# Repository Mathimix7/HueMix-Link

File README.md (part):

<h1 align="center">HueMix-Link</h1>

## Table of Contents

- [Quick Start](#quick-start)
- [Project Overview](#project-overview)
- [Screenshots](#screenshots)
- [What Is In This Repository](#what-is-in-this-repository)
- [System Overview](#system-overview)
- [Prerequisites](#prerequisites)
- [Installation](#installation)
- [First-time Commissioning Workflow](#first-time-commissioning-workflow)
- [ESP Firmware: Build and Flash](#esp-firmware-build-and-flash)
- [Firmware Updates (OTA Page)](#firmware-updates-ota-page)
- [Security v2 Protocol](#security-v2-protocol)
- [Configuration and Data Storage](#configuration-and-data-storage)
- [Networking and Ports](#networking-and-ports)
- [How Automation Works](#how-automation-works)
- [Devices](#devices)
- [License](#license)

## Quick Start

1. Install the backend on a Linux host:

 ```bash
  git clone https://github.com/Mathimix7/HueMix-Link.git
  cd HueMix-Link
  sudo bash install.sh
  ```

1. Open the web UI at `http://huemixlink.local` or your server IP.
2. Pair your Hue Bridge from the Bridge configuration page.
3. Put an ESP device into pairing mode and add it from the Pairing page.
4. Configure the device behavior, then verify it by triggering a button, motion sensor, or lightstrip sync.

## Project Overview

HueMix-Link is a local smart home bridge that connects custom ESP-based devices (gateways, buttons, remotes, motion sensors, door sensors, and lightstrips) to Philips Hue rooms and scenes.

It provides:

- A Flask web UI for setup and management
- A UDP server for low-latency gateway communication
- Automation logic for buttons, remotes, and motion sensors
- OTA firmware update workflows for all device types
- Backup and restore tools for configuration data

## Screenshots

<table width="85%" align="center">
  <tr>
    <td colspan="2" align="center">
      
    </td>
  </tr>
  <tr>
    <td width="50%" align="center">
      
    </td>
    <td width="50%" align="center">
      
    </td>
  </tr>
  <tr>
    <td width="50%" align="center">
      
    </td>
    <td width="50%" align="center">
      
    </td>
  </tr>
</table>

## What Is In This Repository

- `python/`: Main backend service (Flask UI + UDP network + automations + OTA)
- `esp-firmware/`: PlatformIO firmware sources for all device types (gateway, buttons, remotes, motion sensors, door sensors, lightstrips)
- `Hardware-designs/`: KiCad design files for all device types (gateway, buttons, remotes, motion sensors, door sensors, lightstrips)
- `3D Files/`: 3D model files for all device types (STL format for 3D printing)
- `install.sh`: Linux installer/updater
- `VERSION`: Version file for installer/update workflows

## System Overview

### High-level architecture

1. **All ESP devices use ESP-NOW**: Low-power mesh protocol for device-to-device communication
2. **Gateways bridge ESP-NOW to UDP**: Gateways receive ESP-NOW messages and forward them to the backend via UDP
3. **Backend (UDP server) receives events**: Button presses, remote actions, motion detections, device hellos, delivery reports
4. **Automation engine maps events to Hue actions**: Scene activation, toggle on/off, brightness adjust, and lightstrip sync
5. **Hue state is cached and synchronized**: Automations and lightstrips stay aligned with current room/scene state
6. **Web UI for management**: Device pairing, automation configuration, OTA updates, monitoring, and backups

### Main runtime services

- **Flask + Waitress**: Web UI server `127.0.0.1:5001` (default)
- **UDP listener**: Receives gateway messages on `0.0.0.0:7777` (default, configurable)
- **Automation service**: Listens to device events and Hue state changes, applies configured logic
- **OTA manager**: Handles firmware distribution, chunking, and acknowledgment tracking

## Prerequisites

### Software

- Python 3.9+ (3.10+ recommended)
- `pip` and virtual environment support (`venv`)
- Network access to your Hue Bridge (same LAN)
- Linux OS with `systemd` (for production install)
- `sudo` access and `apt` package manager

### Hardware

- At least one Hue Bridge with configured rooms/scenes
- Supported HueMix-Link devices (gateways, buttons, remotes, motion sensors, door sensors, lightstrips)
- Firmware binaries matching your device type and model

## Installation

### Linux

From the repository root:

```bash
sudo bash install.sh
```

The installer will:

- Deploy the Python app to `/opt/huemix-link`
- Create a dedicated service user and Python virtual environment
- Set up a `systemd` service (`huemix-link`) to run on boot
- Configure HAProxy to expose the web app (HTTP port 80, HTTPS port 443 by default)
- Store all runtime data in `/opt/huemix-link/data`

Useful installer options:

```bash
sudo bash install.sh --help           # Show all options
sudo bash install.sh --yes            # Non-interactive install
sudo bash install.sh --dry-run        # Preview without making changes
sudo bash install.sh --force          # Force recreation of venv
sudo bash install.sh --show-version   # Show installed and source versions
sudo bash install.sh --port 8080      # Expose on custom HTTP port
sudo bash install.sh --no-https       # Disable HTTPS (HTTP only)
sudo bash install.sh --no-local       # Skip huemixlink.local hostname setup
```

After installation, the web UI is accessible at:

- `https://huemixlink.local` (or your server IP)
- `http://huemixlink.local` (or your server IP)

### Updating

To update the backend to a newer version, pull the latest code and re-run the installer:

```bash
git pull
sudo bash install.sh
```

The installer detects the existing installation, updates the files, and restarts the service automatically.

## First-time Commissioning Workflow

1. **Start the backend** (automatic on boot if installed via installer)
2. **Open the web UI** at `http://huemixlink.local` (or your server IP)
3. **Configure Hue Bridge**:
   - Go to the Bridge configuration page
   - Auto-discover or enter bridge IP manually
   - Press the Hue Bridge link button
   - Pair app with bridge (saves credentials)
4. **Pair ESP devices**:
   - Go to Pairing page
   - Start pairing window (choose device type if desired)
   - Power on or reset target devices
   - Devices announce themselves via ESP-NOW → gateway → backend
5. **Configure each device**:
    - **Buttons/Remotes**: Map to room + scenes + action behavior (normal, toggle, brightness, scene-cycle)
    - **Motion Sensors**: Set room, time slots, motion actions, after-actions, cooldown periods
    - **Door Sensors**: Set room, open/close actions, and any automation triggers tied to magnetic state changes
    - **Lightstrips**: Assign room, configure LED count/type, optional color scene overrides
    - **Gateways**: Verify online status, mesh routing, LED schedule (day/night auto-off)
6. **Validate behavior** by triggering physical events and checking Hue room/scene changes

## ESP Firmware: Build and Flash

### Flashing ESP devices

**Option 1: Serial flash via OTA page**

1. Go to the **OTA** page in the web UI
2. Select firmware type
3. Connect ESP device via serial in programming mode
4. Click **Flash** and select serial port
5. Monitor progress on the page

**Option 2: Serial port flash**

Use PlatformIO to flash directly via USB:

```bash
cd esp-firmware
pio run -e esp32_net_node --target upload
```

Or use `esptool.py` directly:

```bash
esptool.py --port /dev/ttyUSB0 write_flash 0x0 huemixlink-esp32-net-vX.Y.Z.bin
```

Pre-built firmware binaries are available in the project's GitHub releases. Download the `.bin` file(s) matching your device type and platform.

## Firmware Updates (OTA Page)

The **OTA** page in the web UI lets you:

- **Check available versions** from GitHub releases
- **Web Serial Flasher**: Flash ESP32/ESP8266 devices directly from the browser; v4.x non-gateway firmwares automatically provision a unique 6-digit Security v2 PIN, with one-click **Copy PIN**, **Copy NFC Pairing URL**, and **Print Label** (QR code + PIN)
- **Queued & wake-triggered OTA**: Queue multiple device updates (runs one at a time, automatically ordering radio node before net node on gateways); battery-powered v2 devices can wake and pull queued updates automatically (with a 20% minimum battery guard)
- **Fast v2 OTA**: ESP32 devices on Security v2 use ESP-NOW v2 frames (up to 1024-byte chunks) for 3–5× faster wireless updates
- **Security upgrades & PIN management**: Trigger in-place v1 → v2 upgrades, provision/view 6-digit PINs, and print pairing labels directly from the device list

## Security v2 Protocol

Firmware `4.x` introduces **Security v2**, an authenticated encryption layer over ESP-NOW and UDP that replaces legacy v1 FNV-1a checksums while remaining dual-stack compatible during migration:

- **Authenticated encryption & replay protection**: Every v2 device derives unique per-device `K_own` and `K_ack` keys (via HKDF from the server's master key) during an **X25519 ECDH** 3-flight handshake. All packets are encrypted and authenticated with **AES-128-GCM** and protected against replay attacks by monotonic counters persisted on flash and SQLite.
- **6-digit device PINs**: Non-gateway devices support a write-once 6-digit pairing PIN (auto-provisioned during Web Serial Flashing or sent over an encrypted v2 link from the OTA page) that binds the ECDH handshake against MITM attacks.
- **QR labels & NFC tap-to-pair**: Printable labels include a QR code pointing to `/pairing#pin=XXXXXX`, and the same URL can be written to NTAG NFC stickers. Scanning a label or tapping an NFC tag opens `/pairing` and automatically starts a 60-second v2 pairing window with that PIN (using the `#` URL fragment keeps the PIN out of HTTP server logs).
- **TOFU-only gateways**: Local LAN WiFi and Serial gateways use TOFU Security v2 and auto-pair without requiring PINs.
- **Secure Short-Range Auto-Pairing**: An optional toggle on `/pairing` allows non-revoked Security v2 devices with a saved 6-digit PIN and signal stronger than `-50 dBm` to auto-pair without opening a long-range window (legacy v1, TOFU, and revoked devices are blocked).
- **Migration controls**: Settings provides toggles to enable v2 pairing, require v2 for new pairings, or disable legacy v1 traffic once all devices are upgraded.

## Configuration and Data Storage

All runtime configuration is stored in `python/data/` (or `/opt/huemix-link/data` in production) as JSON files:

- `bridge.json`: Hue bridge IP and app username
- `config.json`: Server settings (UDP port, dev mode)
- `gateways.json`: Known gateway devices
- `buttons.json`: Button and remote configurations
- `motion_sensors.json`: Motion sensor configurations and time slots
- `lightstrips.json`: Lightstrip configurations and color overrides
- `pairing_history.json`: Last 5 paired devices
- `home_id`: Unique 32-bit network identifier for this HueMix-Link instance. In legacy protocol v1, it is mixed into the FNV-1a packet checksum to separate installations (**HomeID is a network identifier, not a cryptographic secret**). See [Security v2 Protocol](#security-v2-protocol) for authenticated encryption.

Backups are created and restored through the settings page; they are stored in `data/backups/`.

## Networking and Ports

- **Web server (internal)**: `127.0.0.1:5001` (Flask)
- **UDP listener (internal)**: `0.0.0.0:7777` (default, receives gateway messages)
- **External HTTP/HTTPS (production)**: Exposed by HAProxy (default HTTP 80 + HTTPS 443)

UDP port can be changed in settings; the backend will restart UDP listening with the new port.

## How Automation Works

1. **Device sends event** via **ESP-NOW** (button press, remote action, motion detection)
2. **Gateway receives** via ESP-NOW and forwards message to backend via **UDP**
3. **UDP server** decodes and validates packet (AES-128-GCM authentication in Security v2, or HomeID checksum in legacy v1)
4. **Device manager** resolves device identity; **pairing manager** verifies eligibility
5. **Automation engine** applies configured logic:
   - **Buttons/Remotes**: Scene cycle, toggle, brightness adjust, hold-to-adjust
   - **Motion Sensors**: Trigger scenes/lights on detection; post-motion fade/off actions; cooldown throttling
6. **Hue API** is called to apply scene/room/light changes
7. **Hue state manager** caches current room, light, and scene state
8. **Lightstrip sync**: Checks if any lightstrips should mirror current scene; sends raw LED commands via **ESP-NOW → gateway → UDP**

On startup, config sync reconciles saved room/scene references against live Hue topology to avoid stale mappings.

## Devices

### Gateway

<table><tr>
  <td></td>
  <td></td>
</tr></table>

The Gateway is a single board that contains two ESP32 modules working together:

- **Net Node** — connects to your home WiFi and bridges between the backend (UDP) and the ESP-NOW mesh. Runs WiFiManager for wireless configuration and relays commands to the radio node over a high-speed UART link.
- **Radio Node** — handles all ESP-NOW communication with peripheral devices (buttons, remotes, sensors, lightstrips) and forwards packets to/from the net node over UART. Extends ESP-NOW coverage independently of WiFi.

**LED indicators**

| LED | State | Meaning |
| ----- | ------- | --------- |
| WiFi | Off | No power / booting |
| WiFi | Fast blink (0.2s) | Not yet configured — WiFi config portal is open |
| WiFi | Slow blink (0.5s) | Connecting or retrying WiFi |
| WiFi | Solid on | Online and operational |
| Data | Brief flash | Packet received or forwarded |
| Data | Breathing (fade in/out) | Net node OTA firmware update in progress |
| Radio | Brief flash | ESP-NOW packet relayed |
| Radio | Breathing (fade in/out) | Radio node OTA firmware update in progress |

**Buttons**

- **Main button**: Acts as a single button that can be mapped to a Hue room in the web UI
- **Aux button**: Hold 5+ seconds to factory-reset and re-open the WiFi config portal

**Initial setup**

1. Power on the gateway — the WiFi LED fast-blinks and it broadcasts SSID `HueMix Link - XXXXXXXX`
2. Connect to that SSID (password: `HueMixLink`) with a phone or laptop
3. Enter your home WiFi credentials and the backend server IP + UDP port
4. The gateway connects, the WiFi LED goes solid, and it sends a HELLO to the backend

**Pairing**

Gateways pair automatically once configured.

**OTA**

Both nodes are updated from the OTA page. Gateways receive OTA directly (no double-press needed).

---

### Radio Gateway (Serial Python)

The Radio Gateway can also run as a serial-connected ESP32 node that pairs with the Python backend instead of WiFi.

- **Net/host side**: Python maintains the gateway state, serial transport, OTA scheduling, and dashboard telemetry
- **Radio side**: ESP32 radio node handles ESP-NOW traffic, OLED status display, and forwards packets over UART
- **LED indicators**: Follows the configured gateway LED schedule; the OLED display also respects the same on/off timing
- **OTA**: Updated from the OTA page using the `gateway_radio_python` firmware target

**Setup**

1. Flash the `esp32_radio_python` firmware
2. Connect the radio node to the backend host over USB serial
3. Configure the serial port in the web UI
4. The backend will sync HOME_ID, gateway state, and dashboard telemetry automatically

---

### Button

<table><tr>
  <td></td>
  <td></td>
</tr></table>

The Button is a single pushbutton device that sends click, hold, and release events via ESP-NOW. The ESP32 version is battery-powered and deep-sleeps between presses, while the ESP8266 version is always-on and runs continuously.

> [!WARNING]
> The `normal_button` firmware is deprecated. The ESP32 Normal Button board v3 and later should use the `remote_button` firmware configured as 1, 2, or 3 buttons.

**Events sent**

| Action | Trigger |
| -------- | --------- |
| Click | Short press and release |
| Holding | Held beyond 500 ms, repeated every 500 ms |
| Release | Released after a hold |

**Default automation** (configurable in web UI): Click cycles scenes in the assigned room. Hold adjusts brightness. Release stops brightness adjustment.

**LED indicators**

| State | Meaning |
| ------- | --------- |
| Brief flash | Action sent via ESP-NOW |
| 2 fast blinks | No acknowledgment — gateway may be out of range |
| 2 slow blinks | Failed to pair device |
| 3 blinks | OTA mode |
| 5 blinks | Device powered on |
| Breathing | OTA in progress |

**Setup and pairing**

1. Flash firmware via serial or the OTA page
2. Open the Pairing page, start a pairing window, then press the button to wake the device
3. After pairing, assign the button to a room in the device settings

**OTA**

**Double-press the reset button** to enter OTA mode — the LED will blink 3 times to confirm. Then initiate the flash from the OTA page.

---

### Remote

<table><tr>
  <td></td>
  <td></td>
</tr></table>

The Remote is a battery-powered ESP32 device with up to 4 independently configurable buttons. Each button can target a different room with its own action type. The number of active buttons (1–4) is configured via hardware at flash time.

**Action types per button** (configurable in web UI)

| Type | Click | Hold |
| ------ | ------- | ------ |
| Normal | Cycle scenes / turn room off | Adjust brightness |
| Toggle | Toggle room on/off | — |
| Brightness Up | Increase brightness | Increase continuously |
| Brightness Down | Decrease brightness | Decrease continuously |
| Scene Cycle | Cycle scenes (no off) | Adjust brightness |

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
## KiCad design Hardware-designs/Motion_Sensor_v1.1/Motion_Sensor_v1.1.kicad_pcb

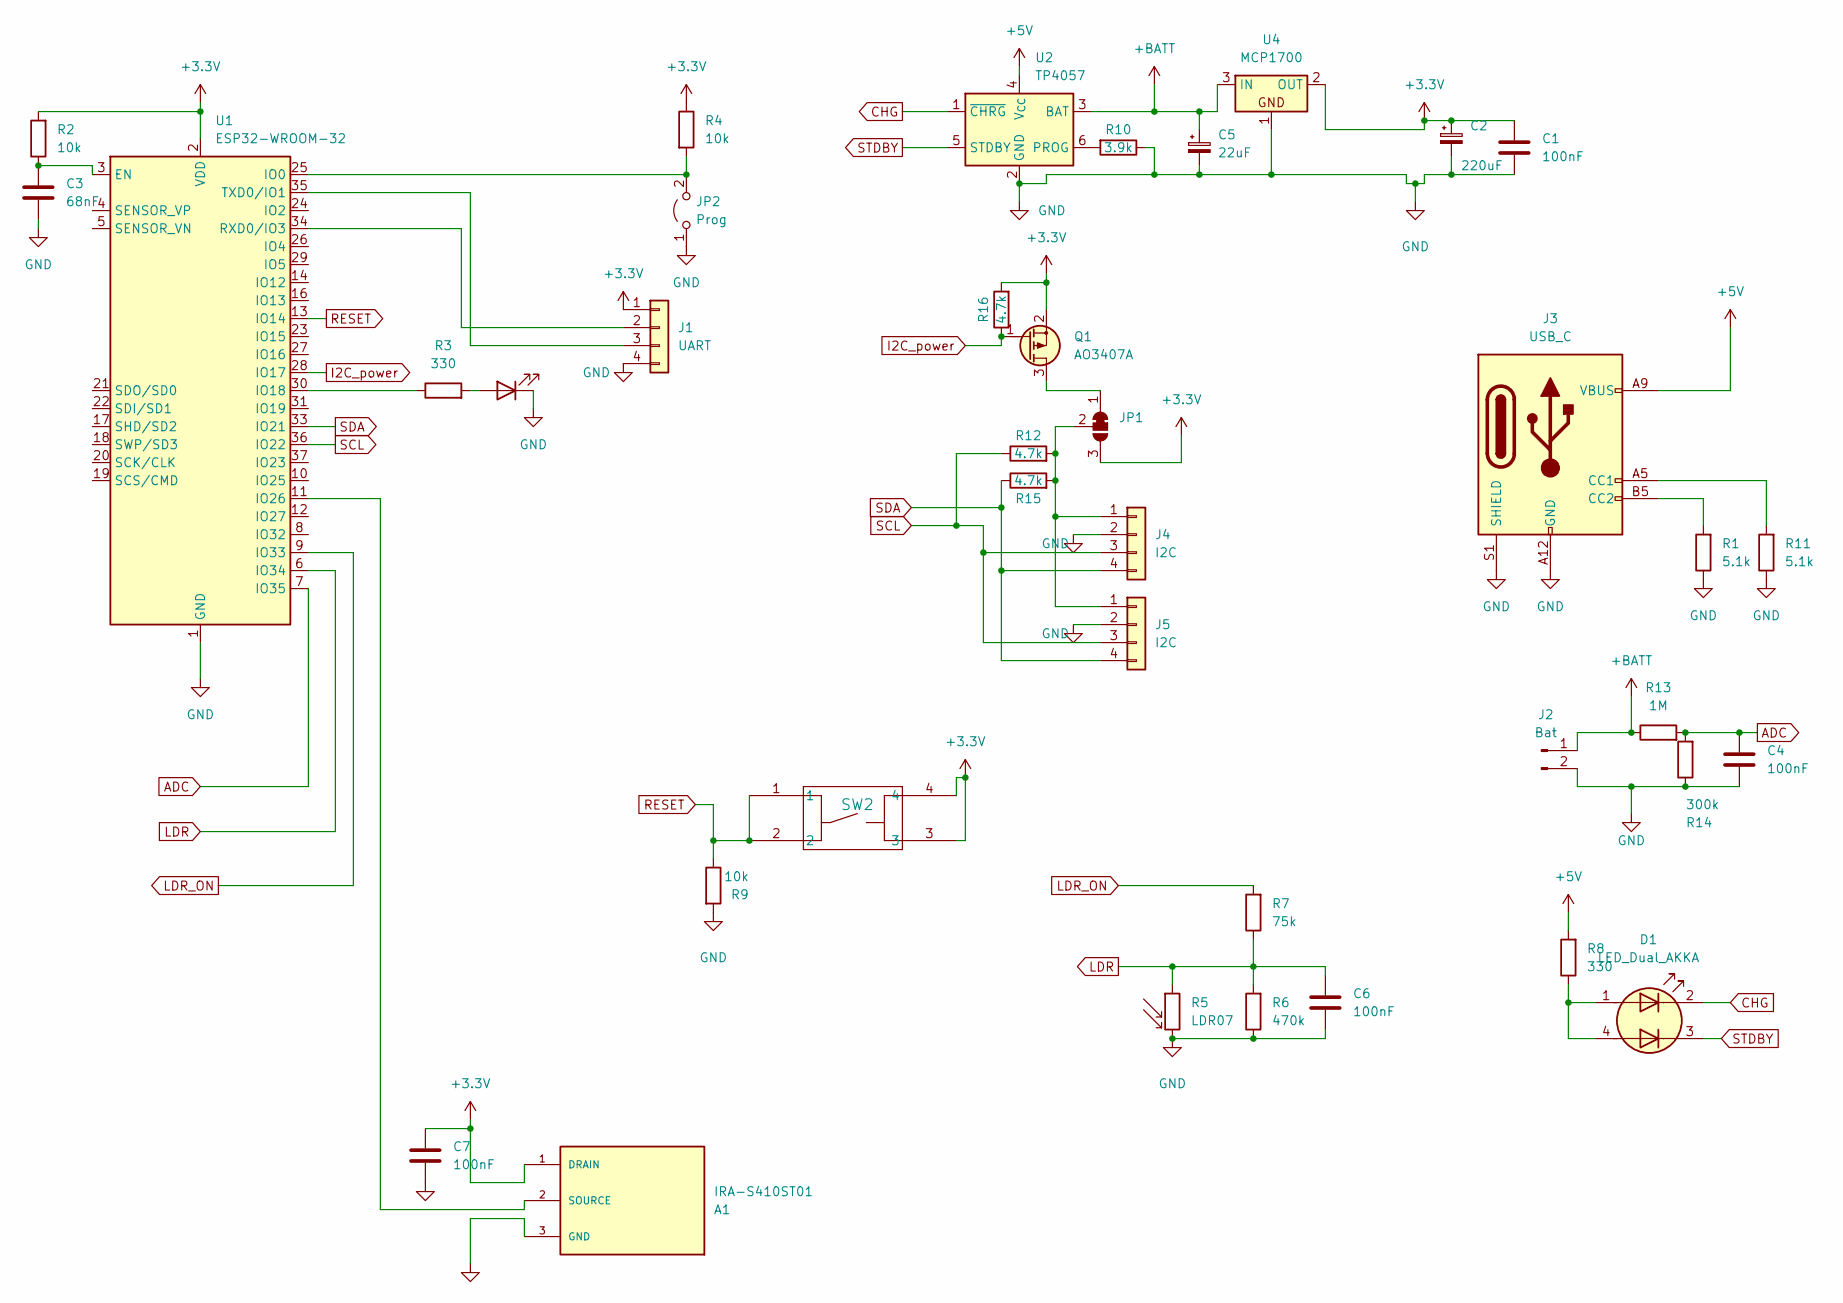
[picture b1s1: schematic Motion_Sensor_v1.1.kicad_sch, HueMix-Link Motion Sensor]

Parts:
A1: IRA-S410ST01; TO254P940H490-3
C1, C4, C6, C7: 100nF; C_0805_2012Metric_Pad1.18x1.45mm_HandSolder
C2: 220uF; CP_EIA-6032-15_Kemet-U_HandSolder
C3: 68nF; C_0805_2012Metric_Pad1.18x1.45mm_HandSolder
C5: 22uF; CP_EIA-6032-15_Kemet-U_HandSolder
D1: LED_Dual_AKKA; APHBM2012ETSGTC
D3: LED; LED_1206_3216Metric
J1: UART; PinHeader_1x04_P2.54mm_Vertical
J2: Bat; TestPoint_2Pads_Pitch2.54mm_Drill0.8mm
J3: USB_C; USB_C_Receptacle_GCT_USB4125-xx-x-0190_6P_TopMnt_Horizontal
J4, J5: I2C; PinHeader_1x04_P2.54mm_Vertical
JP1: SolderJumper_3_Bridged12; SolderJumper-3_P1.3mm_Bridged12_RoundedPad1.0x1.5mm
JP2: Prog; PinHeader_1x02_P2.54mm_Vertical
Q1: AO3407A; SOT-23
R1, R11: 5.1k; R_1206_3216Metric_Pad1.30x1.75mm_HandSolder
R2, R4, R9: 10k; R_1206_3216Metric_Pad1.30x1.75mm_HandSolder
R3, R8: 330; R_1206_3216Metric_Pad1.30x1.75mm_HandSolder
R5: LDR07; R_LDR_5.1x4.3mm_P3.4mm_Vertical
R6: 470k; R_1206_3216Metric_Pad1.30x1.75mm_HandSolder
R7: 75k; R_1206_3216Metric_Pad1.30x1.75mm_HandSolder
R10: 3.9k; R_1206_3216Metric_Pad1.30x1.75mm_HandSolder
R12, R15, R16: 4.7k; R_1206_3216Metric_Pad1.30x1.75mm_HandSolder
R13: 1M; R_1206_3216Metric_Pad1.30x1.75mm_HandSolder
R14: 300k; R_1206_3216Metric_Pad1.30x1.75mm_HandSolder
SW2: PTS526 SM15 SMTR2 LFS; SMT_FS
U1: ESP32-WROOM-32; ESP32-WROOM-32D
U2: TP4057; TSOT-23-6_HandSoldering
U4: MCP1700; SOT-23

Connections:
+3.3V: A1.1 (DRAIN), C1.1, C2.1, C7.1, J1.1, JP1.3 (B), Q1.2 (S), R2.2, R4.1, R16.2, SW2.3, SW2.4, U1.2 (VDD), U4.2 (OUT)
+5V: J3.A9 (VBUS), J3.B9 (VBUS), R8.2, U2.4 (V_{CC})
+BATT: C5.1, J2.1, R13.1, U2.3 (BAT), U4.3 (IN)
ADC: C4.1, R13.2, R14.2, U1.7 (IO35)
CHG: D1.2 (K1), U2.1 (~CHRG)
GND: A1.3 (GND), C1.2, C2.2, C3.2, C4.2, C5.2, C6.2, C7.2, D3.1 (K), J1.4, J2.2, J3.A12 (GND), J3.B12 (GND), J3.S1 (SHIELD), J4.2, J5.2, JP2.1 (A), R1.1, R5.2, R6.1, R9.2, R10.1, R11.1, R14.1, U1.1 (GND), U1.15 (GND), U1.38 (GND), U1.39 (GND), U2.2 (GND), U4.1
I2C_power: Q1.1 (G), R16.1, U1.28 (IO17)
LDR: C6.1, R5.1, R6.2, R7.1, U1.6 (IO34)
LDR_ON: R7.2, U1.9 (IO33)
unnamed: A1.2 (SOURCE), U1.11 (IO26)
unnamed: D1.1 (A1), D1.4 (A2), R8.1
unnamed: D3.2 (A), R3.2
unnamed: J1.2, U1.34 (RXD0/IO3)
unnamed: J1.3, U1.35 (TXD0/IO1)
unnamed: J3.A5 (CC1), R11.2
unnamed: J3.B5 (CC2), R1.2
unnamed: J4.1, J5.1, JP1.2 (C), R12.2, R15.2
unnamed: JP1.1 (A), Q1.3 (D)
unnamed: JP2.2 (B), R4.2, U1.25 (IO0)
unnamed: C3.1, R2.1, U1.3 (EN)
unnamed: R3.1, U1.30 (IO18)
unnamed: R10.2, U2.6 (PROG)
RESET: R9.1, SW2.1, SW2.2, U1.13 (IO14)
SCL: J4.3, J5.3, R12.1, U1.36 (IO22)
SDA: J4.4, J5.4, R15.1, U1.33 (IO21)
STDBY: D1.3 (K2), U2.5 (STDBY)

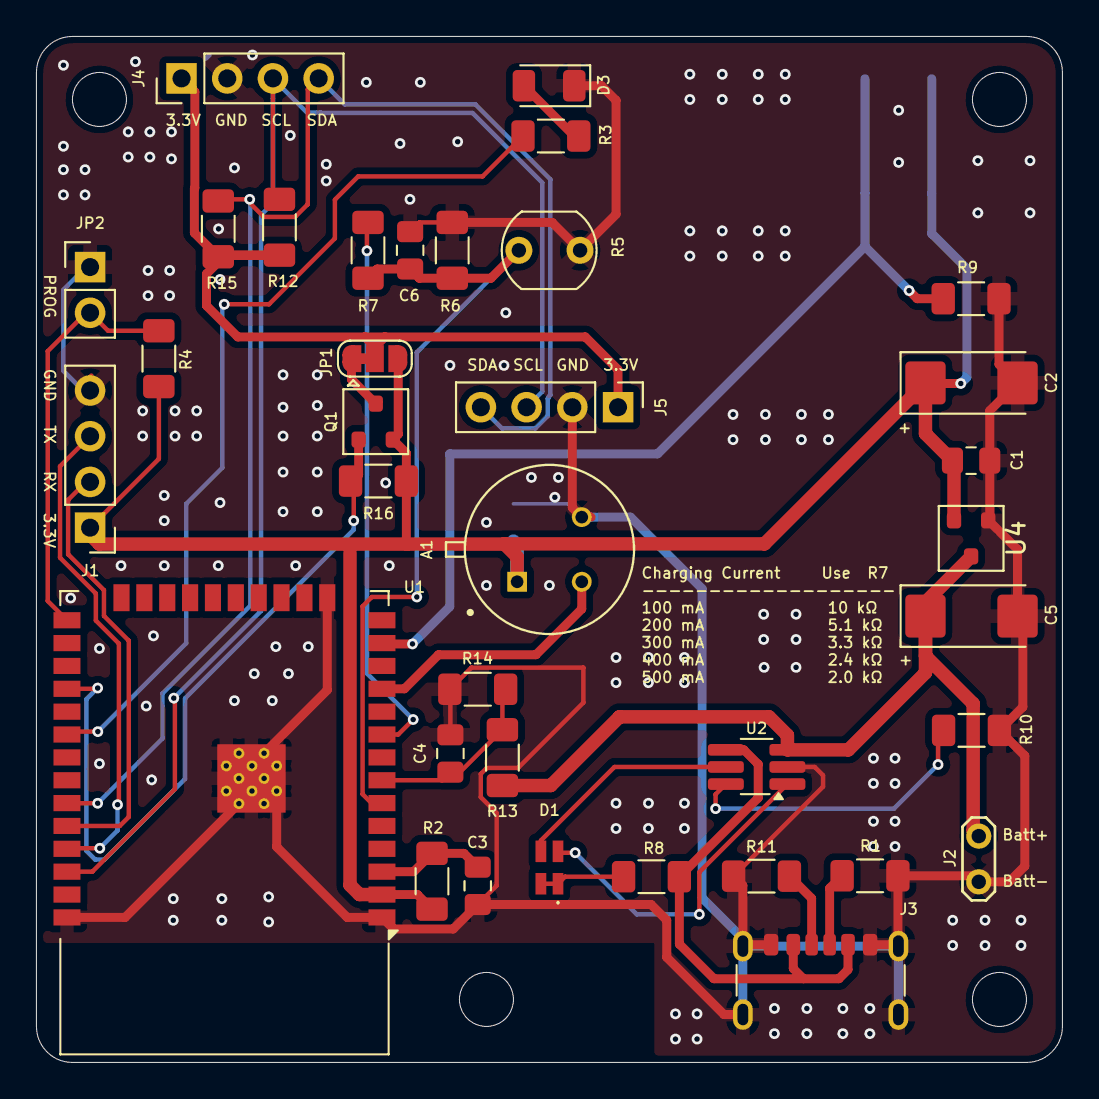
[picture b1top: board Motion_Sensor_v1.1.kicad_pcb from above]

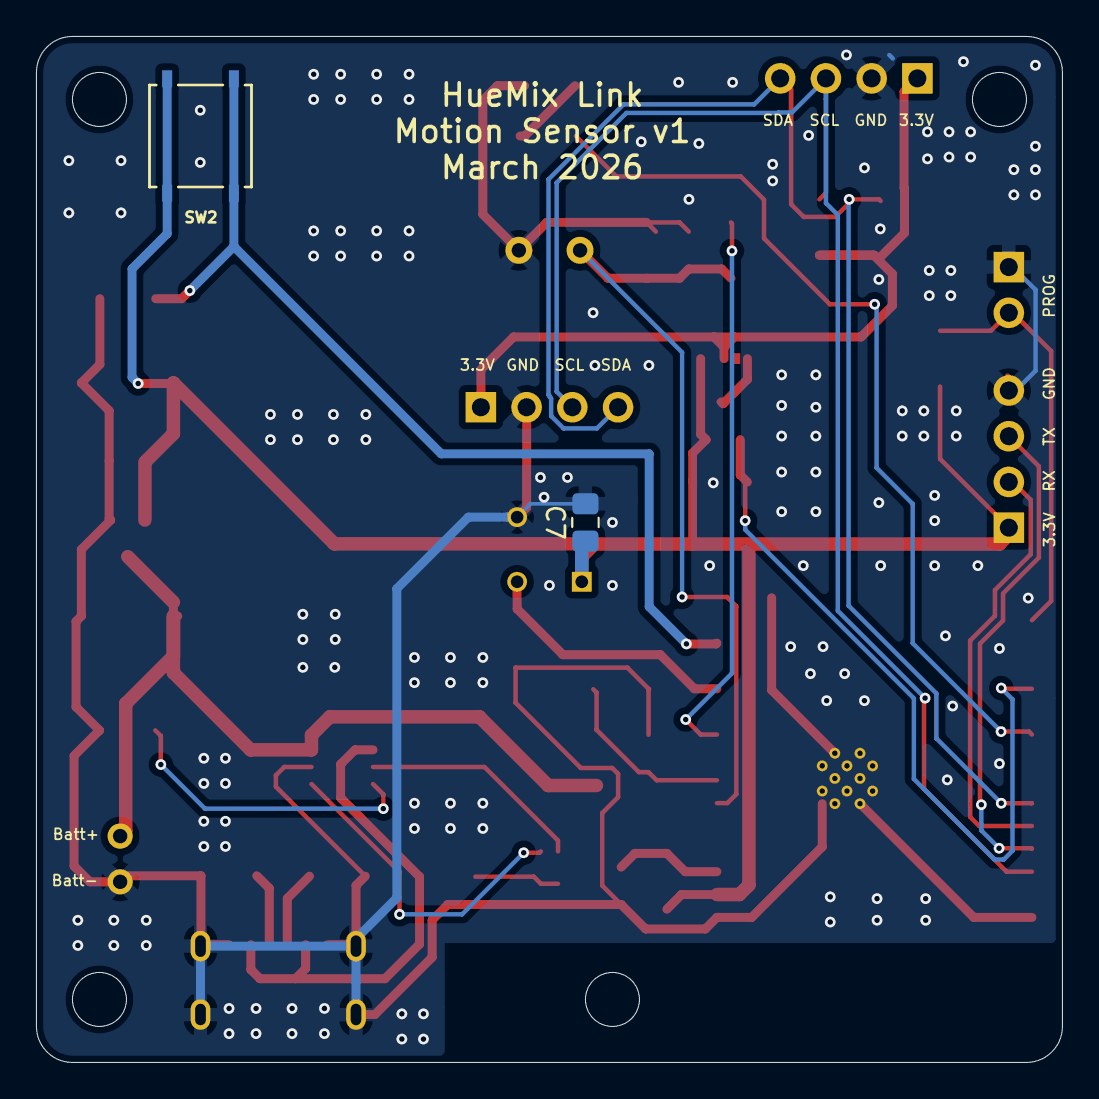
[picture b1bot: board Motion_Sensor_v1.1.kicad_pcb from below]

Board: 2 copper layers, 57.0 x 57.0 mm, 38 parts (2 on the bottom side), 26 nets.

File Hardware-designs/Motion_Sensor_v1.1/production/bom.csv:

Designator,Footprint,Quantity,Value,LCSC Part #
A1,TO254P940H490-3,1,IRA-S410ST01,
"C1, C4, C6, C7",0805,4,100nF,
C2,CP_EIA-6032-15_Kemet-U_HandSolder,1,220uF,
C3,0805,1,68nF,
C5,CP_EIA-6032-15_Kemet-U_HandSolder,1,22uF,
D1,APHBM2012ETSGTC,1,LED_Dual_AKKA,
D3,1206,1,LED,
J1,PinHeader_1x04_P2.54mm_Vertical,1,UART,
J2,TestPoint_2Pads_Pitch2.54mm_Drill0.8mm,1,Bat,
J3,USB_C_Receptacle_GCT_USB4125-xx-x-0190_6P_TopMnt_Horizontal,1,USB_C,
"J4, J5",PinHeader_1x04_P2.54mm_Vertical,2,I2C,
JP2,PinHeader_1x02_P2.54mm_Vertical,1,Prog,
Q1,SOT-23,1,AO3407A,
"R1, R11",1206,2,5.1k,
R10,1206,1,3.9k,
"R12, R15, R16",1206,3,4.7k,
R13,1206,1,1M,
R14,1206,1,300k,
"R2, R4, R9",1206,3,10k,
"R3, R8",1206,2,330,
R5,R_LDR_5.1x4.3mm_P3.4mm_Vertical,1,LDR07,
R6,1206,1,470k,
R7,1206,1,75k,
SW2,SMT_FS,1,PTS526 SM15 SMTR2 LFS,
U1,ESP32-WROOM-32D,1,ESP32-WROOM-32,
U2,TSOT-23-6_HandSoldering,1,TP4057,
U4,SOT-23,1,MCP1700,

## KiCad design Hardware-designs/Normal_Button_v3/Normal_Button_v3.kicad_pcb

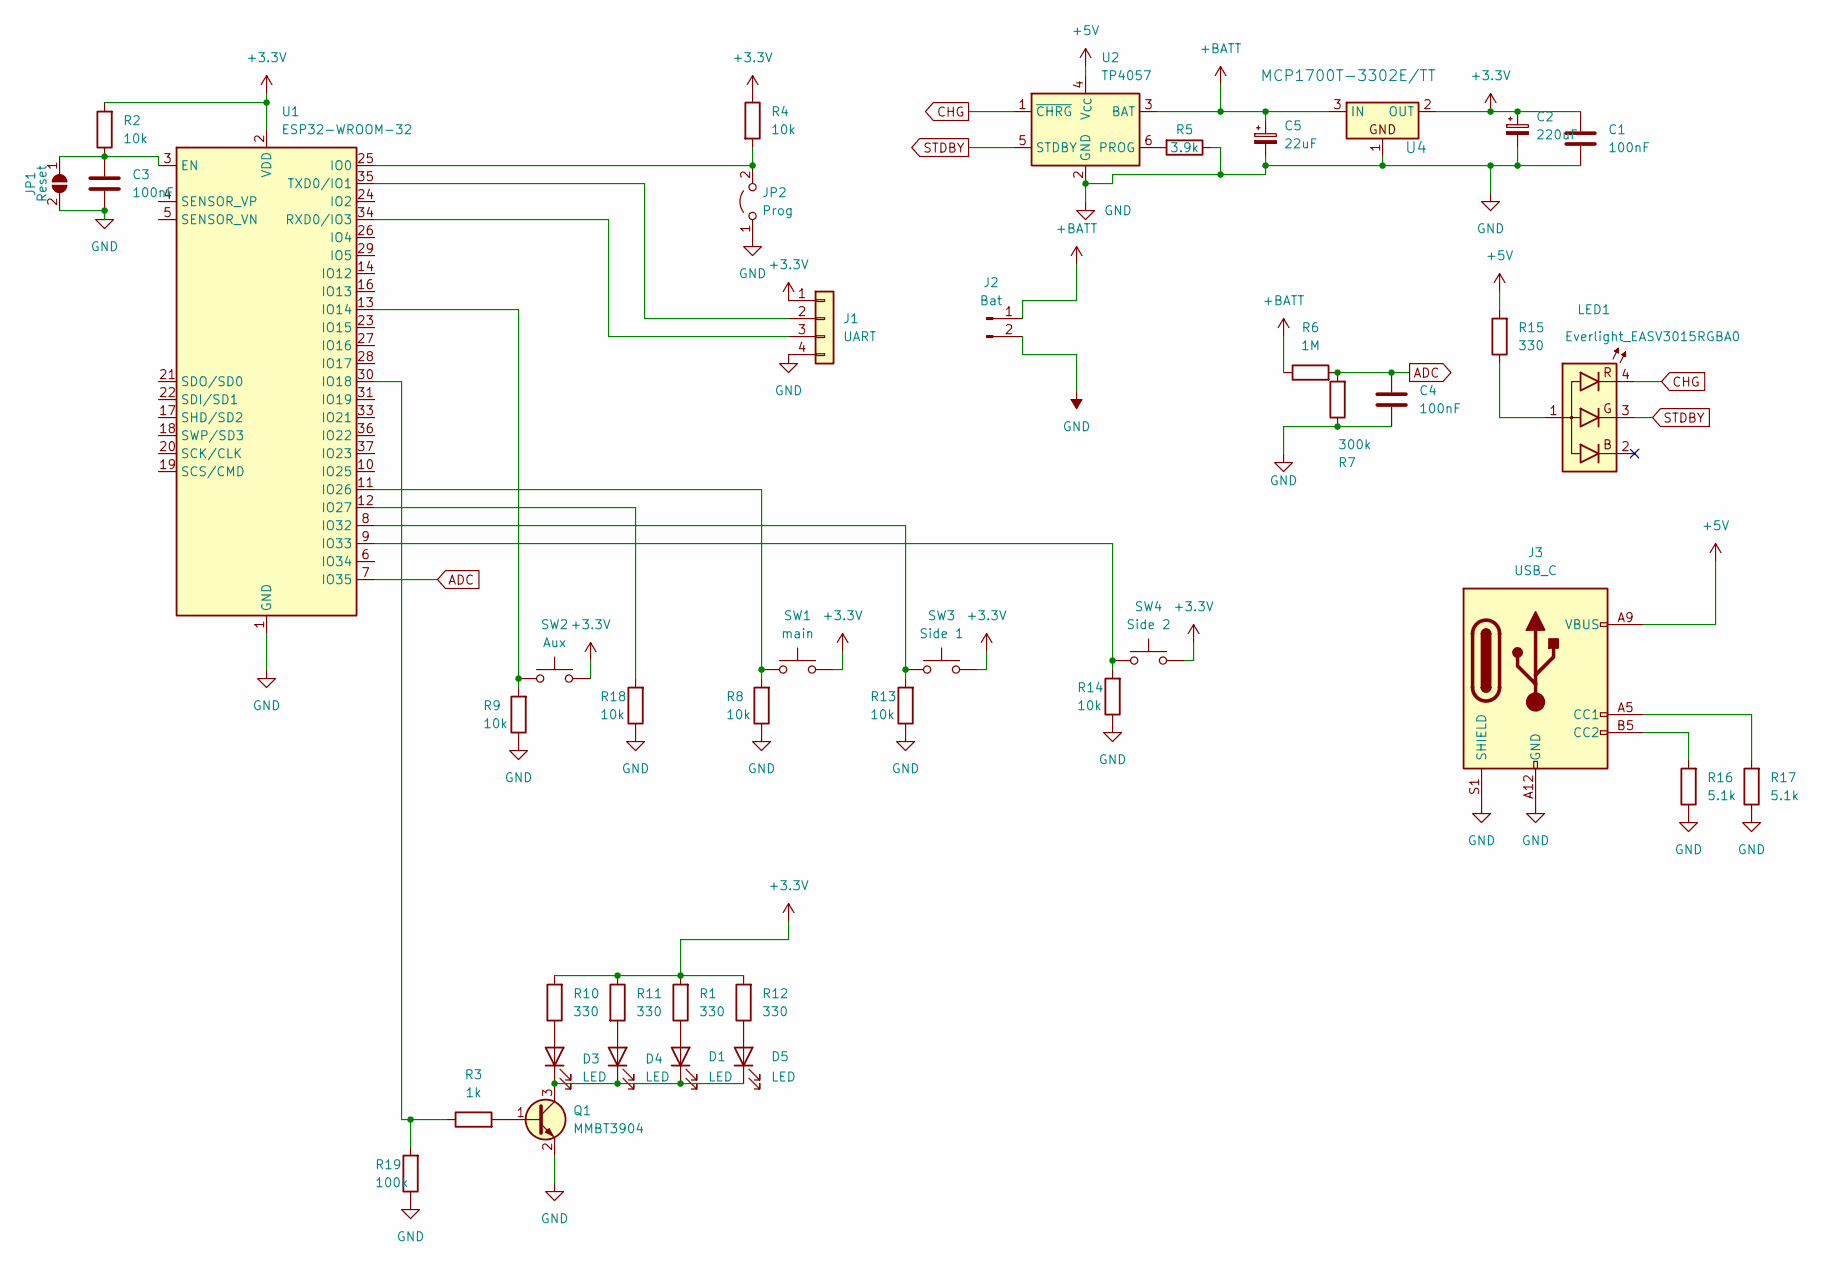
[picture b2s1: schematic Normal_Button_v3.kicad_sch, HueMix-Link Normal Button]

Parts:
C1, C3, C4: 100nF; C_0805_2012Metric_Pad1.18x1.45mm_HandSolder
C2: 220uF; CP_EIA-6032-15_Kemet-U_HandSolder
C5: 22uF; CP_EIA-6032-15_Kemet-U_HandSolder
D1, D3, D4, D5: LED; LED_D3.0mm
J1: UART; PinHeader_1x04_P2.54mm_Vertical
J2: Bat; JST_EH_B2B-EH-A_1x02_P2.50mm_Vertical
J3: USB_C; USB_C_Receptacle_GCT_USB4125-xx-x-0190_6P_TopMnt_Horizontal
JP1: Reset; SolderJumper-2_P1.3mm_Open_Pad1.0x1.5mm
JP2: Prog; PinHeader_1x02_P2.54mm_Vertical
LED1: Everlight_EASV3015RGBA0; LED_D5.0mm-4_RGB
Q1: MMBT3904; SOT-23
R1, R10, R11, R12, R15: 330; R_1206_3216Metric_Pad1.30x1.75mm_HandSolder
R2, R4, R8, R9, R13, R14, R18: 10k; R_1206_3216Metric_Pad1.30x1.75mm_HandSolder
R3: 1k; R_1206_3216Metric_Pad1.30x1.75mm_HandSolder
R5: 3.9k; R_1206_3216Metric_Pad1.30x1.75mm_HandSolder
R6: 1M; R_1206_3216Metric_Pad1.30x1.75mm_HandSolder
R7: 300k; R_1206_3216Metric_Pad1.30x1.75mm_HandSolder
R16, R17: 5.1k; R_1206_3216Metric_Pad1.30x1.75mm_HandSolder
R19: 100k; R_1206_3216Metric_Pad1.30x1.75mm_HandSolder
SW1: main; SW_PUSH-12mm
SW2: Aux; SW_PUSH_6mm
SW3: Side 1; SW_PUSH-12mm
SW4: Side 2; SW_PUSH-12mm
U1: ESP32-WROOM-32; ESP32-WROOM-32E
U2: TP4057; TSOT-23-6_HandSoldering
U4: MCP1700T-3302E/TT; SOT-23

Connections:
+3.3V: C1.1, C2.1, J1.1, R1.2, R2.2, R4.1, R10.2, R11.1, R12.2, SW1.2, SW2.2, SW3.2, SW4.2, U1.2 (VDD), U4.2 (OUT)
+5V: J3.A9 (VBUS), J3.B9 (VBUS), R15.2, U2.4 (V_{CC})
+BATT: C5.1, J2.1, R6.1, U2.3 (BAT), U4.3 (IN)
ADC: C4.1, R6.2, R7.2, U1.7 (IO35)
CHG: LED1.4 (R), U2.1 (~CHRG)
GND: C1.2, C2.2, C3.2, C4.2, C5.2, J1.4, J2.2, J3.A12 (GND), J3.B12 (GND), J3.S1 (SHIELD), JP1.2 (B), JP2.1 (A), Q1.2 (E), R5.1, R7.1, R8.1, R9.1, R13.1, R14.1, R16.1, R17.1, R18.1, R19.1, U1.1 (GND), U1.15 (GND), U1.38 (GND), U1.39 (GND), U2.2 (GND), U4.1
unnamed: D1.2 (A), R1.1
unnamed: D1.1 (K), D3.1 (K), D4.1 (K), D5.1 (K), Q1.3 (C)
unnamed: D3.2 (A), R10.1
unnamed: D4.2 (A), R11.2
unnamed: D5.2 (A), R12.1
unnamed: J1.2, U1.35 (TXD0/IO1)
unnamed: J1.3, U1.34 (RXD0/IO3)
unnamed: J3.A5 (CC1), R17.2
unnamed: J3.B5 (CC2), R16.2
unnamed: C3.1, JP1.1 (A), R2.1, U1.3 (EN)
unnamed: JP2.2 (B), R4.2, U1.25 (IO0)
unnamed: LED1.1 (A), R15.1
unnamed: Q1.1 (B), R3.2
unnamed: R9.2, SW2.1, U1.13 (IO14)
unnamed: R3.1, R19.2, U1.30 (IO18)
unnamed: R8.2, SW1.1, U1.11 (IO26)
unnamed: R18.2, U1.12 (IO27)
unnamed: R13.2, SW3.1, U1.8 (IO32)
unnamed: R14.2, SW4.1, U1.9 (IO33)
unnamed: R5.2, U2.6 (PROG)
STDBY: LED1.3 (G), U2.5 (STDBY)

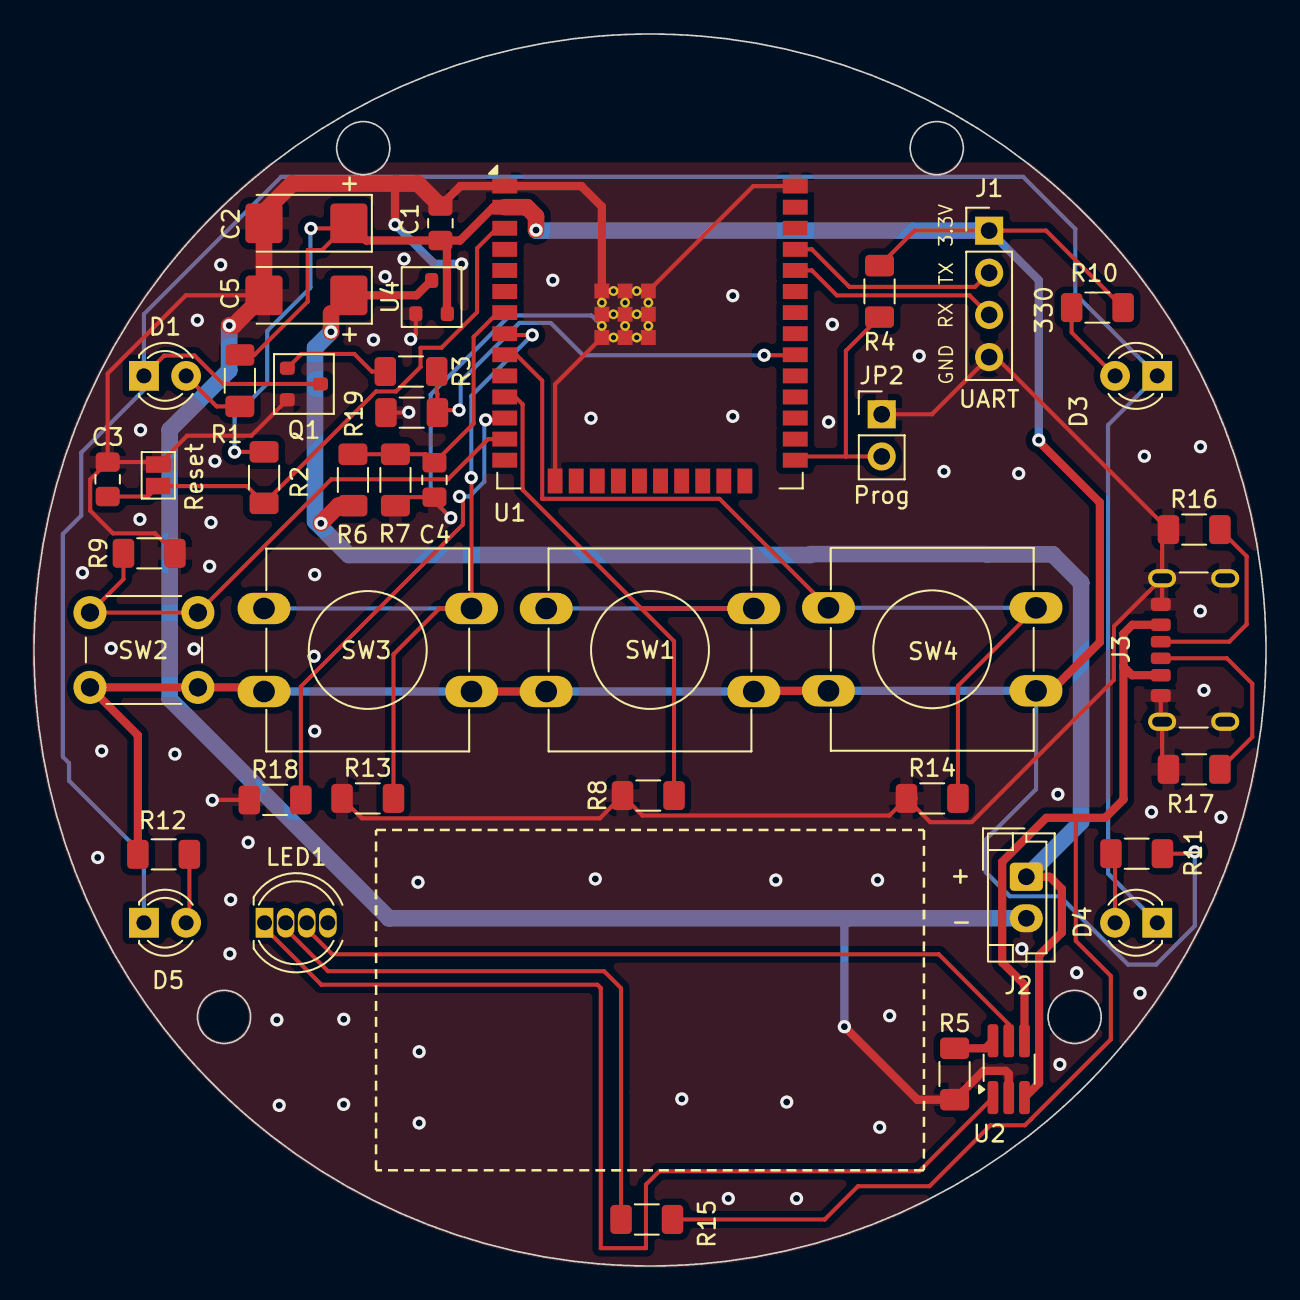
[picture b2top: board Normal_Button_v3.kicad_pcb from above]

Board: 2 copper layers, 74.2 x 74.2 mm, 42 parts (0 on the bottom side), 27 nets.

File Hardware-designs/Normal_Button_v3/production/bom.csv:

Designator,Footprint,Quantity,Value,LCSC Part #
"C1, C4",0805,2,100nF,
C2,CP_EIA-6032-15_Kemet-U_HandSolder,1,220uF,
C3,0805,1,68nF,
C5,CP_EIA-6032-15_Kemet-U_HandSolder,1,22uF,
"D1, D3, D4, D5",LED_D3.0mm,4,LED,
J1,PinHeader_1x04_P2.54mm_Vertical,1,UART,
J2,JST_EH_B2B-EH-A_1x02_P2.50mm_Vertical,1,Bat,
J3,USB_C_Receptacle_GCT_USB4125-xx-x-0190_6P_TopMnt_Horizontal,1,USB_C,
JP1,SolderJumper-2_P1.3mm_Open_Pad1.0x1.5mm,1,Reset,
JP2,PinHeader_1x02_P2.54mm_Vertical,1,Prog,
LED1,LED_D5.0mm-4_RGB,1,Everlight_EASV3015RGBA0,
Q1,SOT-23,1,MMBT3904,
"R1, R10, R11, R12, R15",1206,5,330,
"R13, R14, R18, R2, R4, R8, R9",1206,7,10k,
"R16, R17",1206,2,5.1k,
R19,1206,1,100k,
R3,1206,1,1k,
R5,1206,1,3.9k,
R6,1206,1,1M,
R7,1206,1,300k,
SW1,SW_PUSH-12mm,1,main,
SW2,SW_PUSH_6mm,1,Aux,
SW3,SW_PUSH-12mm,1,Side 1,
SW4,SW_PUSH-12mm,1,Side 2,
U1,ESP32-WROOM-32E,1,ESP32-WROOM-32,
U2,TSOT-23-6_HandSoldering,1,TP4057,
U4,SOT-23,1,MCP1700T-3302E/TT,

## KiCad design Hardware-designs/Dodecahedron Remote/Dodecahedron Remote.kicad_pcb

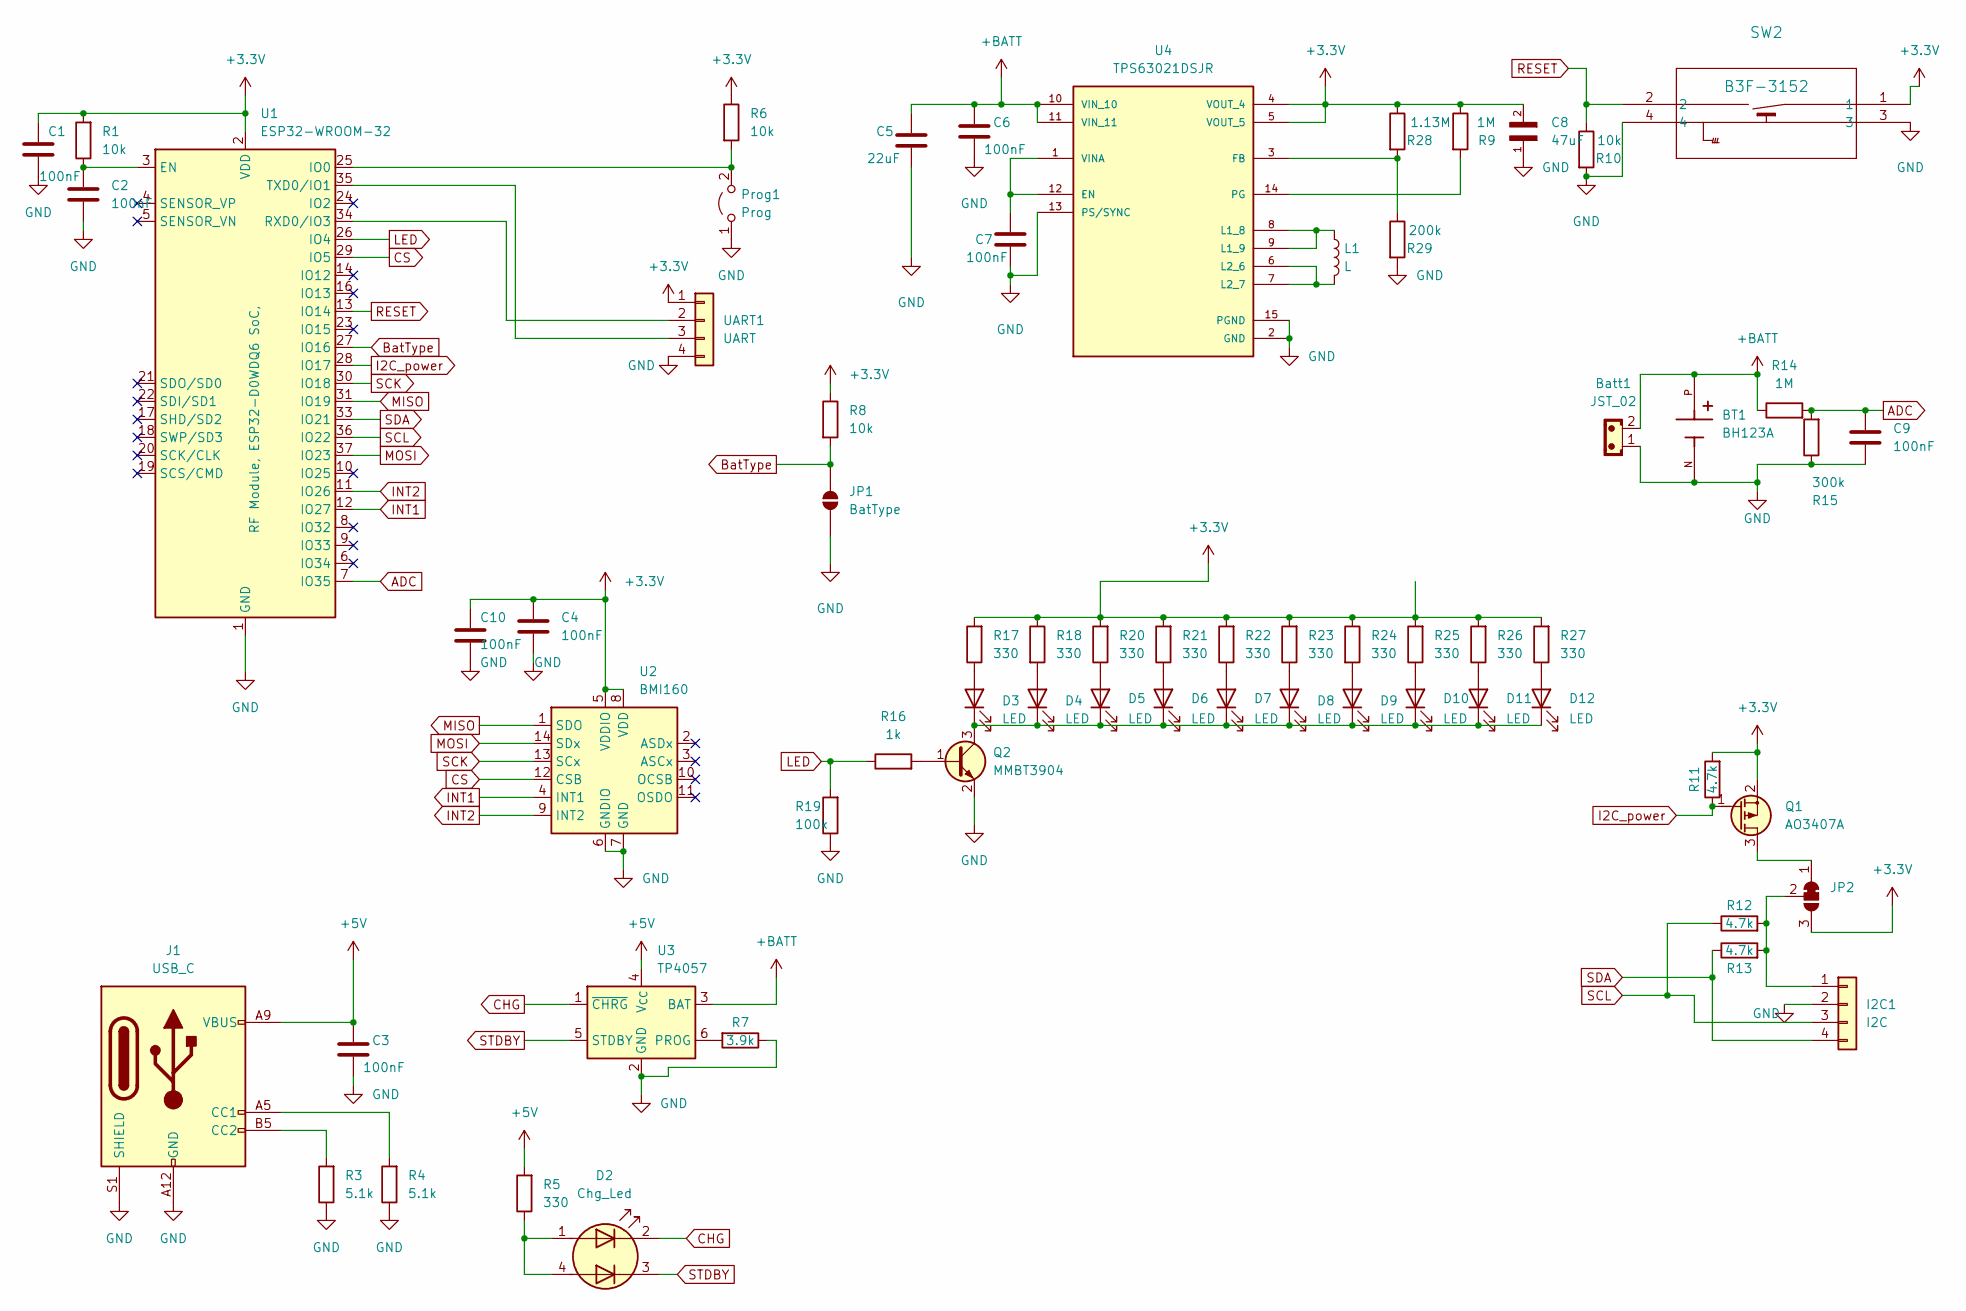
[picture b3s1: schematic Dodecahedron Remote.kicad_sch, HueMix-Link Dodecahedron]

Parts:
BT1: BH123A; BAT_BH123A; PARTREV E
Batt1: JST_02; JST_EH_B2B-EH-A_1x02_P2.50mm_Vertical
C1, C2, C3, C4, C6, C7, C9, C10: 100nF; C_0603_1608Metric_Pad1.08x0.95mm_HandSolder
C5: 22uF; C_0603_1608Metric_Pad1.08x0.95mm_HandSolder
C8: 47uF; CAPC2012X145N; PARTREV NA
D2: Chg_Led; APHBM2012ETSGTC
D3, D4, D5, D6, D7, D8, D9, D10, D11, D12: LED; LED_1206_3216Metric_Pad1.42x1.75mm_HandSolder
I2C1: I2C; PinHeader_1x04_P2.54mm_Vertical
J1: USB_C; USB_C_Receptacle_GCT_USB4125-xx-x-0190_6P_TopMnt_Horizontal
JP1: BatType; SolderJumper-2_P1.3mm_Open_RoundedPad1.0x1.5mm
JP2: SolderJumper_3_Bridged12; SolderJumper-3_P1.3mm_Bridged12_RoundedPad1.0x1.5mm
L1: L; L_Murata_DFE201610P
Prog1: Prog; PinHeader_1x02_P2.54mm_Vertical
Q1: AO3407A; SOT-23
Q2: MMBT3904; SOT-23
R1, R6, R8, R10: 10k; R_0603_1608Metric_Pad0.98x0.95mm_HandSolder
R3, R4: 5.1k; R_0603_1608Metric_Pad0.98x0.95mm_HandSolder
R5, R17, R18, R20, R21, R22, R23, R24, R25, R26, R27: 330; R_0603_1608Metric_Pad0.98x0.95mm_HandSolder
R7: 3.9k; R_0603_1608Metric_Pad0.98x0.95mm_HandSolder
R9, R14: 1M; R_0603_1608Metric_Pad0.98x0.95mm_HandSolder
R11, R12, R13: 4.7k; R_0603_1608Metric_Pad0.98x0.95mm_HandSolder
R15: 300k; R_0603_1608Metric_Pad0.98x0.95mm_HandSolder
R16: 1k; R_0603_1608Metric_Pad0.98x0.95mm_HandSolder
R19: 100k; R_0603_1608Metric_Pad0.98x0.95mm_HandSolder
R28: 1.13M; R_0603_1608Metric_Pad0.98x0.95mm_HandSolder
R29: 200k; R_0603_1608Metric_Pad0.98x0.95mm_HandSolder
SW2: B3F-3152; SW_SPST_Omron_B3F-315x_Angled
U1: ESP32-WROOM-32
U2: BMI160; Bosch_LGA-14_3x2.5mm_P0.5mm
U3: TP4057; TSOT-23-6_HandSoldering
U4: TPS63021DSJR; IC_TPS63021DSJR; PARTREV I
UART1: UART; PinHeader_1x04_P2.54mm_Vertical

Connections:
+3.3V: C1.1, C4.1, C8.2, C10.1, JP2.3 (B), Q1.2 (S), R1.2, R6.1, R8.1, R9.1, R11.2, R17.2, R18.1, R20.2, R21.2, R22.2, R23.2, R24.1, R25.2, R26.2, R27.2, R28.1, SW2.1, U1.2 (VDD), U2.5 (VDDIO), U2.8 (VDD), U4.4 (VOUT_4), U4.5 (VOUT_5), UART1.1
+5V: C3.1, J1.A9 (VBUS), J1.B9 (VBUS), R5.2, U3.4 (V_{CC})
+BATT: BT1.P, Batt1.2, C5.1, C6.1, R14.1, U3.3 (BAT), U4.10 (VIN_10), U4.11 (VIN_11)
ADC: C9.1, R14.2, R15.2, U1.7 (IO35)
BatType: JP1.2 (B), R8.2, U1.27 (IO16)
CHG: D2.2 (K1), U3.1 (~CHRG)
CS: U1.29 (IO5), U2.12 (CSB)
GND: BT1.N, Batt1.1, C1.2, C2.2, C3.2, C4.2, C5.2, C6.2, C7.2, C8.1, C9.2, C10.2, I2C1.2, J1.A12 (GND), J1.B12 (GND), J1.S1 (SHIELD), JP1.1 (A), Prog1.1 (A), Q2.2 (E), R3.1, R4.1, R7.1, R10.2, R15.1, R19.1, R29.2, SW2.3, SW2.4, U1.1 (GND), U1.15 (GND), U1.38 (GND), U1.39 (GND), U2.6 (GNDIO), U2.7 (GND), U3.2 (GND), U4.2 (GND), U4.13 (PS/SYNC), U4.15 (PGND), UART1.4
I2C_power: Q1.1 (G), R11.1, U1.28 (IO17)
INT1: U1.12 (IO27), U2.4 (INT1)
INT2: U1.11 (IO26), U2.9 (INT2)
LED: R16.1, R19.2, U1.26 (IO4)
MISO: U1.31 (IO19), U2.1 (SDO)
MOSI: U1.37 (IO23), U2.14 (SDx)
unnamed: D2.1 (A1), D2.4 (A2), R5.1
unnamed: D3.2 (A), R17.1
unnamed: D4.2 (A), R18.2
unnamed: D5.2 (A), R20.1
unnamed: D6.2 (A), R21.1
unnamed: D7.2 (A), R22.1
unnamed: D8.2 (A), R23.1
unnamed: D9.2 (A), R24.2
unnamed: D10.2 (A), R25.1
unnamed: D3.1 (K), D4.1 (K), D5.1 (K), D6.1 (K), D7.1 (K), D8.1 (K), D9.1 (K), D10.1 (K), D11.1 (K), D12.1 (K), Q2.3 (C)
unnamed: D11.2 (A), R26.1
unnamed: D12.2 (A), R27.1
unnamed: I2C1.1, JP2.2 (C), R12.2, R13.2
unnamed: J1.A5 (CC1), R4.2
unnamed: J1.B5 (CC2), R3.2
unnamed: JP2.1 (A), Q1.3 (D)
unnamed: Prog1.2 (B), R6.2, U1.25 (IO0)
unnamed: Q2.1 (B), R16.2
unnamed: C2.1, R1.1, U1.3 (EN)
unnamed: U1.34 (RXD0/IO3), UART1.2
unnamed: U1.35 (TXD0/IO1), UART1.3
unnamed: R7.2, U3.6 (PROG)
unnamed: C7.1, U4.1 (VINA), U4.12 (EN)
unnamed: R28.2, R29.1, U4.3 (FB)
unnamed: L1.1, U4.8 (L1_8), U4.9 (L1_9)
unnamed: L1.2, U4.6 (L2_6), U4.7 (L2_7)
unnamed: R9.2, U4.14 (PG)
RESET: R10.1, SW2.2, U1.13 (IO14)
SCK: U1.30 (IO18), U2.13 (SCx)
SCL: I2C1.3, R12.1, U1.36 (IO22)
SDA: I2C1.4, R13.1, U1.33 (IO21)
STDBY: D2.3 (K2), U3.5 (STDBY)

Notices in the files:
README.md:
This project is licensed under the terms in `LICENSE`.
